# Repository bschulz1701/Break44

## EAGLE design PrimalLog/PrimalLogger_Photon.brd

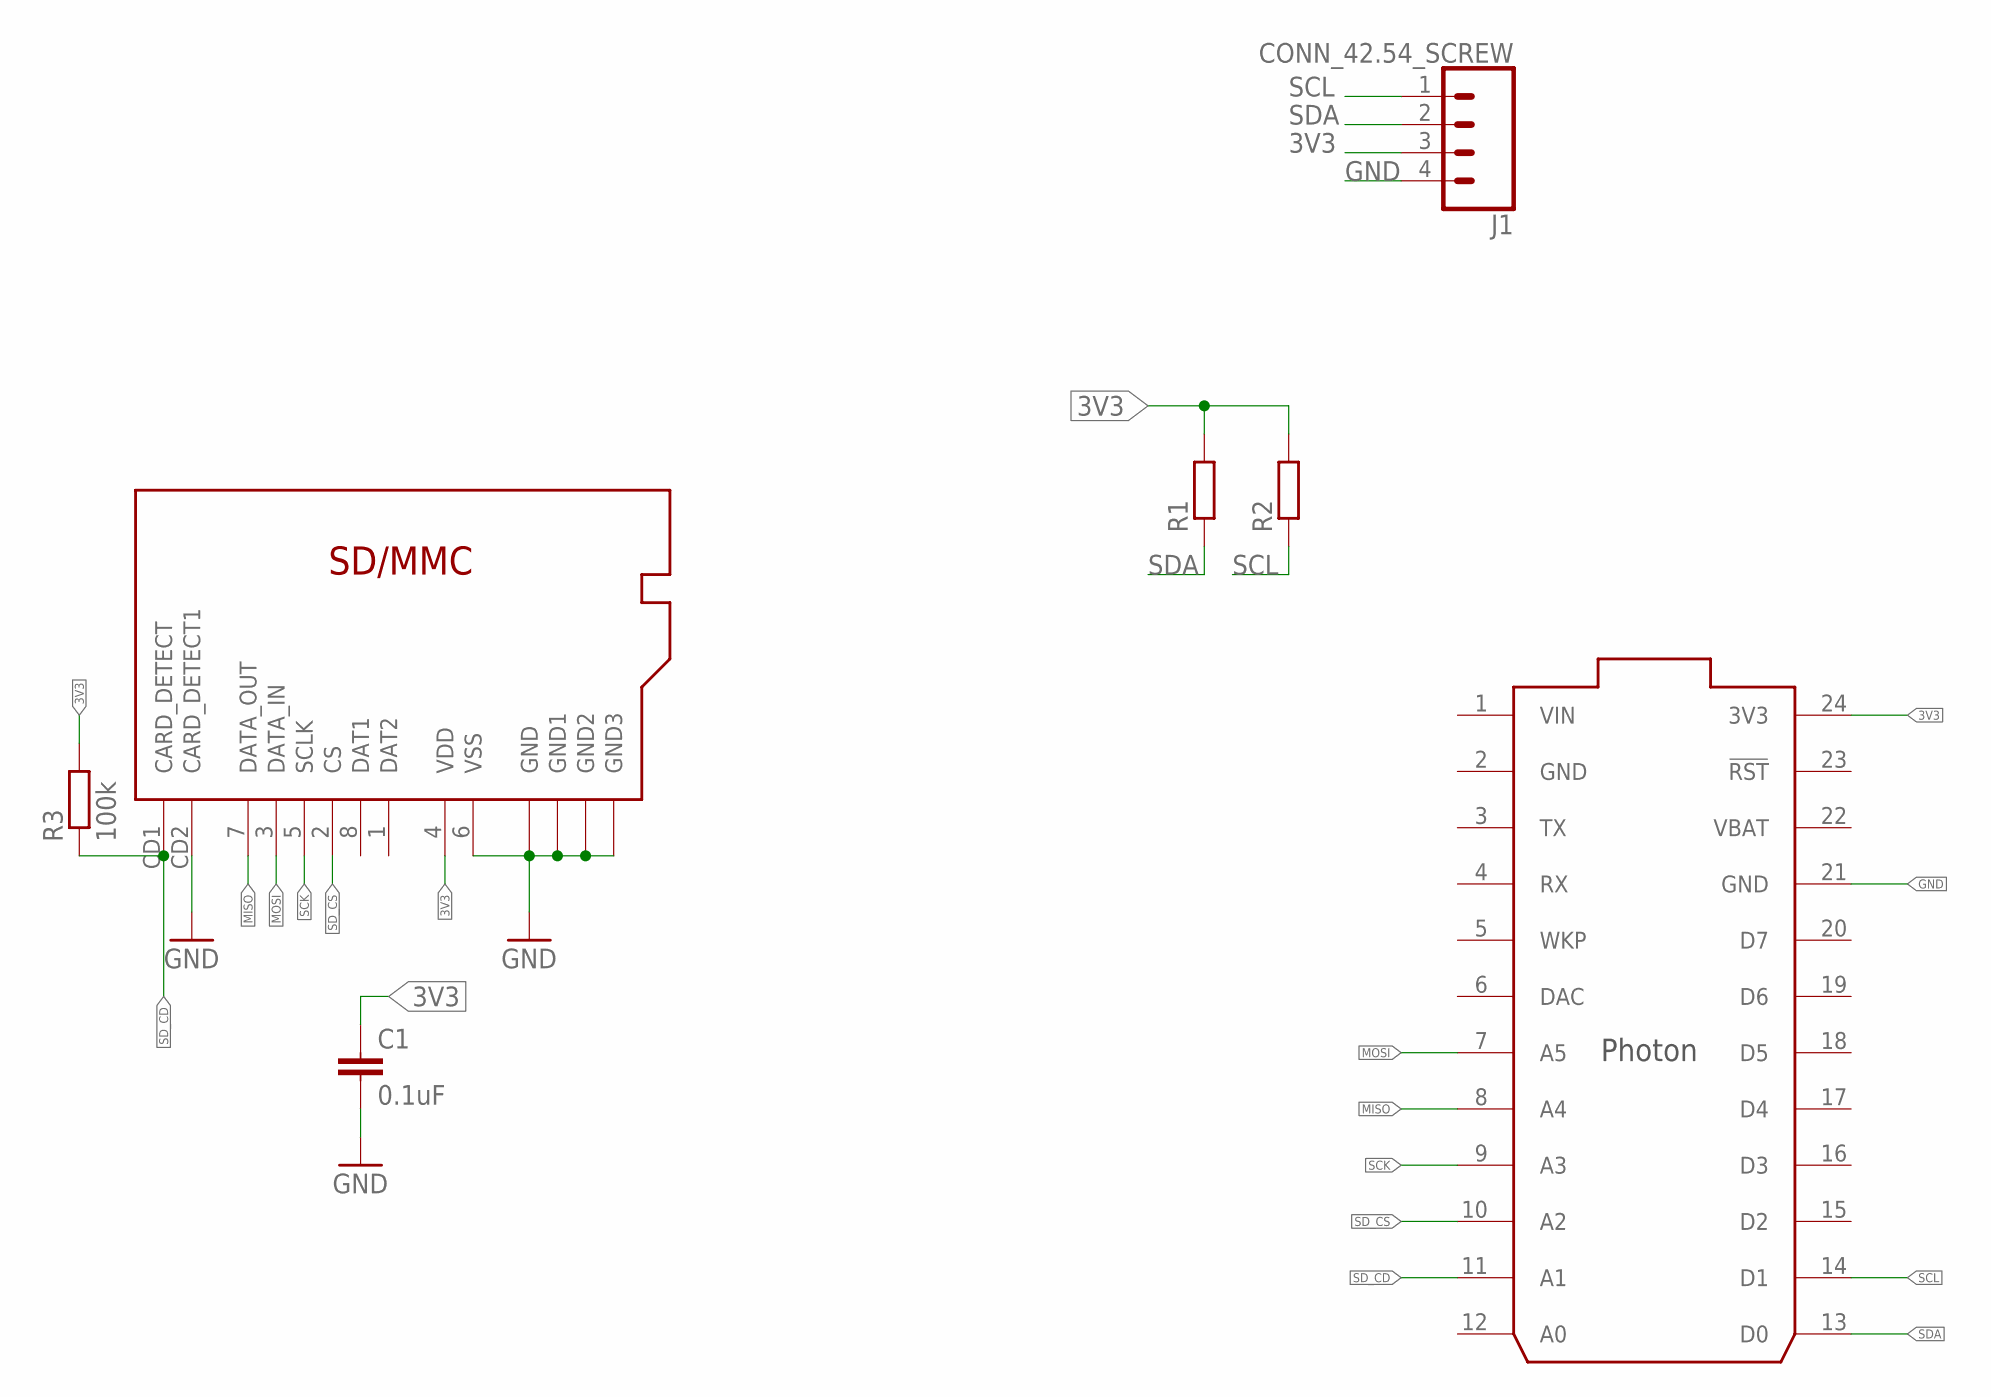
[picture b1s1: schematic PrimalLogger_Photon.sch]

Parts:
C1: 0.1uF; C0603
J1: CONN_42.54_SCREW; 1X04_SCREW
R1, R2: R-EU_10KR0603; R0603
R3: 100k; R0603
SD1: MICRO_SD; CUSTOM-PARTS_SD_MICRO
U$1: PHOTON_NO_SILK

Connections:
3V3: C1.1, J1.3, R1.2, R2.2, R3.2, SD1.4 (VDD), U$1.24 (3V3)
GND: C1.2, J1.4, SD1.6 (VSS), SD1.CD2 (CARD_DETECT1), SD1.GND@1 (GND), SD1.GND@2 (GND1), SD1.GND@3 (GND2), SD1.GND@5 (GND3), U$1.2 (GND), U$1.21 (GND)
MISO: SD1.7 (DATA_OUT), U$1.8 (A4)
MOSI: SD1.3 (DATA_IN), U$1.7 (A5)
SCK: SD1.5 (SCLK), U$1.9 (A3)
SCL: J1.1, R2.1, U$1.14 (D1)
SDA: J1.2, R1.1, U$1.13 (D0)
SD_CD: R3.1, SD1.CD1 (CARD_DETECT), U$1.11 (A1)
SD_CS: SD1.2 (CS), U$1.10 (A2)
VBAT: U$1.22 (VBAT)
VIN: U$1.1 (VIN)

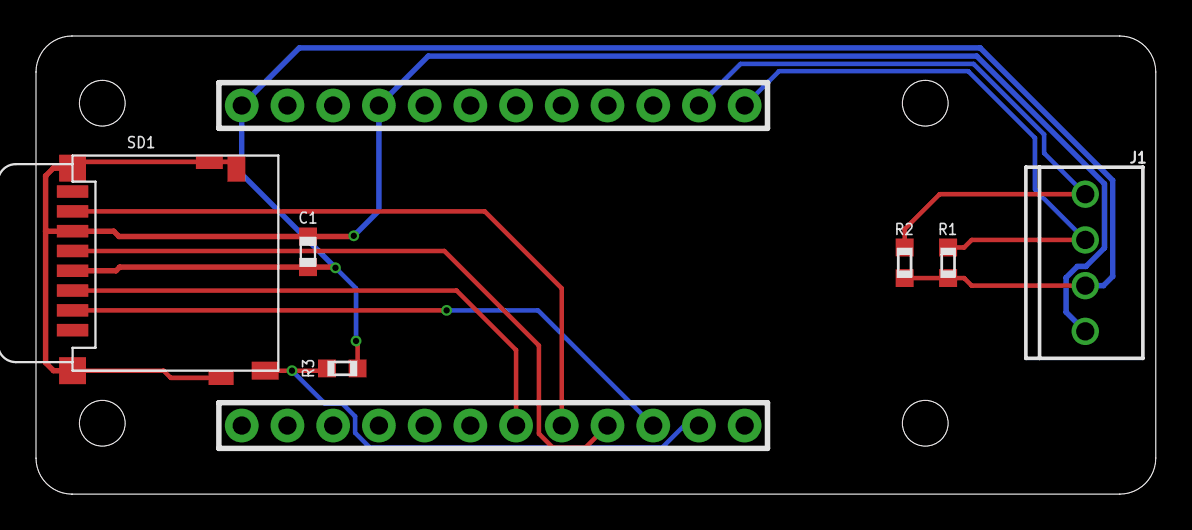
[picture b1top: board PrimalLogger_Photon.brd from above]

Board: 2 copper layers, 62.2 x 25.5 mm, 7 parts (0 on the bottom side), 9 nets.

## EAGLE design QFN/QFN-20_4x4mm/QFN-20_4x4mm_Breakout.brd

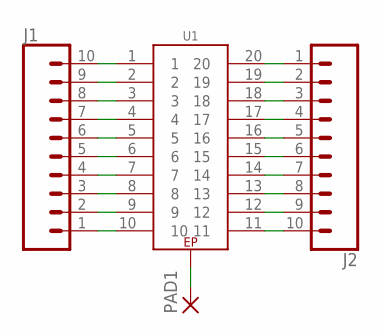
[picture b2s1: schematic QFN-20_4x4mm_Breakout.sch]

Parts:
J1, J2: CONN_10"; 1X10
PAD1: SMD2; SMD1,27-2,54
U1: GEN_20_EPQFN-20_4X4; QFN20

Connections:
unnamed: PAD1.1, U1.EP
unnamed: J1.10, U1.1
unnamed: J1.9, U1.2
unnamed: J1.8, U1.3
unnamed: J1.7, U1.4
unnamed: J1.6, U1.5
unnamed: J1.5, U1.6
unnamed: J1.4, U1.7
unnamed: J1.3, U1.8
unnamed: J1.2, U1.9
unnamed: J1.1, U1.10
unnamed: J2.10, U1.11
unnamed: J2.9, U1.12
unnamed: J2.8, U1.13
unnamed: J2.7, U1.14
unnamed: J2.6, U1.15
unnamed: J2.5, U1.16
unnamed: J2.4, U1.17
unnamed: J2.3, U1.18
unnamed: J2.2, U1.19
unnamed: J2.1, U1.20

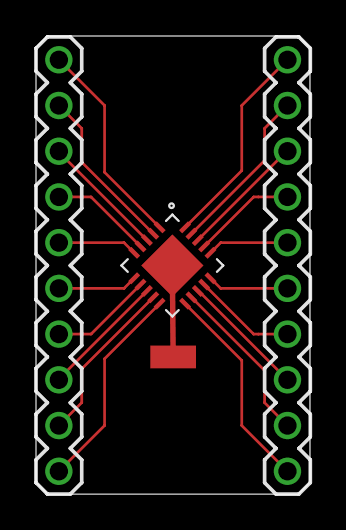
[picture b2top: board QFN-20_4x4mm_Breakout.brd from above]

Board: 2 copper layers, 15.2 x 25.5 mm, 4 parts (0 on the bottom side), 21 nets.

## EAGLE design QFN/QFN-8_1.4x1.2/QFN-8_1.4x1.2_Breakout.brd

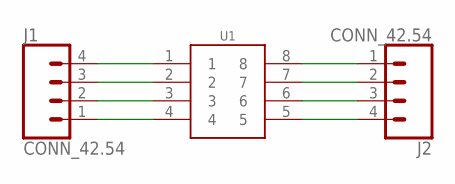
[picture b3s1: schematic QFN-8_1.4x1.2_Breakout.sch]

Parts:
J1, J2: CONN_42.54; 1X04
U1: GEN_8QFN_1.4X1.2; UQFN-8_1.4X1.2

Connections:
unnamed: J1.4, U1.1
unnamed: J1.3, U1.2
unnamed: J1.2, U1.3
unnamed: J1.1, U1.4
unnamed: J2.4, U1.5
unnamed: J2.3, U1.6
unnamed: J2.2, U1.7
unnamed: J2.1, U1.8

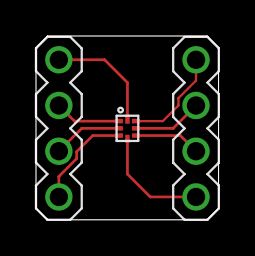
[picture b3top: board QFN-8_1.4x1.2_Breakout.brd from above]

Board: 2 copper layers, 10.1 x 10.2 mm, 3 parts (0 on the bottom side), 8 nets.

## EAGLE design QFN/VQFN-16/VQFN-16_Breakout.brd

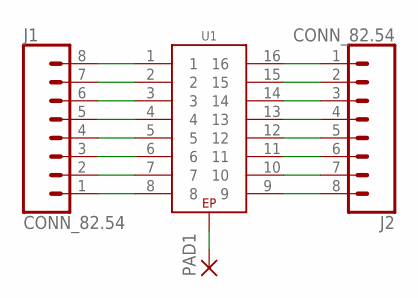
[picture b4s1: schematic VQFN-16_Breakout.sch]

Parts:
J1, J2: CONN_82.54; 1X08
PAD1: SMD2; SMD1,27-2,54
U1: GEN_16_EPVQFN-16; VQFN-16

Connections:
unnamed: PAD1.1, U1.EP
unnamed: J1.8, U1.1
unnamed: J1.7, U1.2
unnamed: J1.6, U1.3
unnamed: J1.5, U1.4
unnamed: J1.4, U1.5
unnamed: J1.3, U1.6
unnamed: J1.2, U1.7
unnamed: J1.1, U1.8
unnamed: J2.8, U1.9
unnamed: J2.7, U1.10
unnamed: J2.6, U1.11
unnamed: J2.5, U1.12
unnamed: J2.4, U1.13
unnamed: J2.3, U1.14
unnamed: J2.2, U1.15
unnamed: J2.1, U1.16

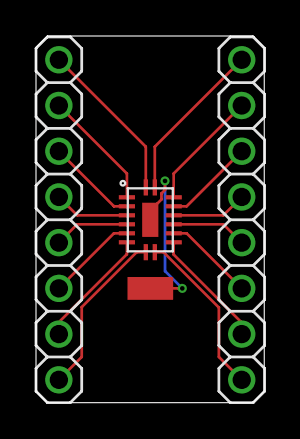
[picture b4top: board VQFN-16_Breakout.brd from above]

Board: 2 copper layers, 12.7 x 20.4 mm, 4 parts (0 on the bottom side), 17 nets.

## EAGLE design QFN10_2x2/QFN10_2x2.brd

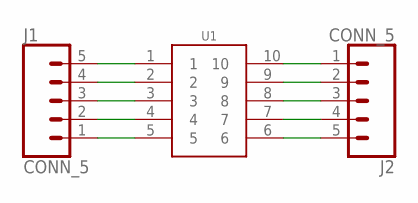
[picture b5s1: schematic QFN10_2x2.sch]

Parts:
J1, J2: CONN_5; 1X05
U1: GEN_10QFN10_2X2; QFN10_SI114X

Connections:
unnamed: J1.5, U1.1
unnamed: J1.4, U1.2
unnamed: J1.3, U1.3
unnamed: J1.2, U1.4
unnamed: J1.1, U1.5
unnamed: J2.5, U1.6
unnamed: J2.4, U1.7
unnamed: J2.3, U1.8
unnamed: J2.2, U1.9
unnamed: J2.1, U1.10

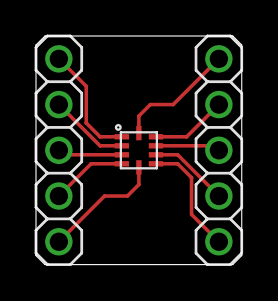
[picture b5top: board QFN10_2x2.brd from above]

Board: 2 copper layers, 11.4 x 12.7 mm, 3 parts (0 on the bottom side), 10 nets.

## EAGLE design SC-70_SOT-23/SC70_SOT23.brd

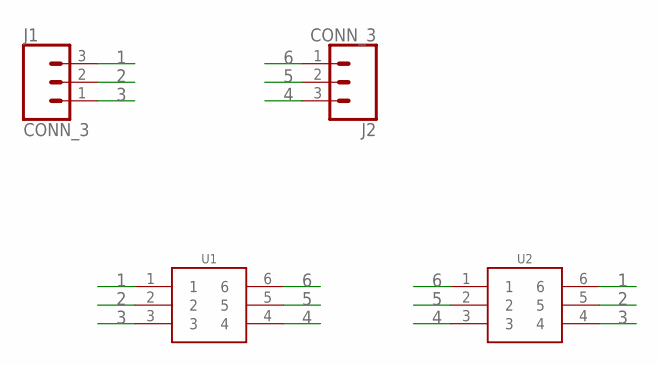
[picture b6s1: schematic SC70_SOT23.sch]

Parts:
J1, J2: CONN_3; 1X03
U1: GEN_6SC-70; DCK_R-PDSO-G6
U2: GEN_6SOT-23; DDC_R-PDSO-G6

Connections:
1: J1.3, U1.1, U2.6
2: J1.2, U1.2, U2.5
3: J1.1, U1.3, U2.4
4: J2.3, U1.4, U2.3
5: J2.2, U1.5, U2.2
6: J2.1, U1.6, U2.1

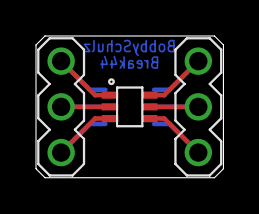
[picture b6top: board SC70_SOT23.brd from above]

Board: 2 copper layers, 10.4 x 7.9 mm, 4 parts (1 on the bottom side), 6 nets.
